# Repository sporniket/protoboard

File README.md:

# Sporniket's protoboard

> [WARNING] Please read carefully this note before using this project. It contains important facts.

Content

1. What is **Sporniket's protoboard**, and when to use it ?
2. What should you know before using **Sporniket's protoboard** ?
3. How to use **Sporniket's protoboard** ?
4. Known issues
5. Miscellanous

## 1. What is **Sporniket's protoboard**, and when to use it ?

**Sporniket's protoboard** is a custom prototyping board with 976 points arranged like a breadboard, that fits inside a 10cm×11cm rectangle.

This is a project designed with [Kicad](https://www.kicad.org/), version 7.

### Gallery

### Licence

**Sporniket's protoboard** is marked with CC0 1.0 Universal. To view a copy of this license, visit http://creativecommons.org/publicdomain/zero/1.0

**Sporniket's protoboard** is distributed in the hope that it will be useful, but WITHOUT ANY WARRANTY; without even the implied warranty of SAFETY, MERCHANTABILITY or FITNESS FOR A PARTICULAR PURPOSE.

### Releases notes

#### v1.0.0

* Initial release, schematics and gerbers.

## 2. What should you know before using **Sporniket's protoboard** ?

**Sporniket's protoboard** is designed using [Kicad](https://www.kicad.org/), version 7.

> Do not use **Sporniket's protoboard** if this project is not suitable for your project.

## 3. How to use **Sporniket's protoboard** ?

### From sources

To get the latest available models, one must clone the git repository.

	git clone https://github.com/sporniket/protoboard.git

Then, open the project in Kicad.

### From github releases

A github **schematic only** release (with `schematics` in the release tag and name) will provide a PDF of the schematics

A github **regular** release will provide :

* A standalone Kicad project
* A PDF of the schematics
* A PDF of the silkscreen
* If applicable, a Gerber for boardmanufacturer. Some details may have been adapted for a specific manufacturer.
* If applicable, a BOM, and pick an place files, likely for a specific manufacturer too.

## 4. Known issues
See the [project issues](https://github.com/sporniket/protoboard/issues) page.

## 5. Miscellanous

### Report issues
Use the [project issues](https://github.com/sporniket/protoboard/issues) page.

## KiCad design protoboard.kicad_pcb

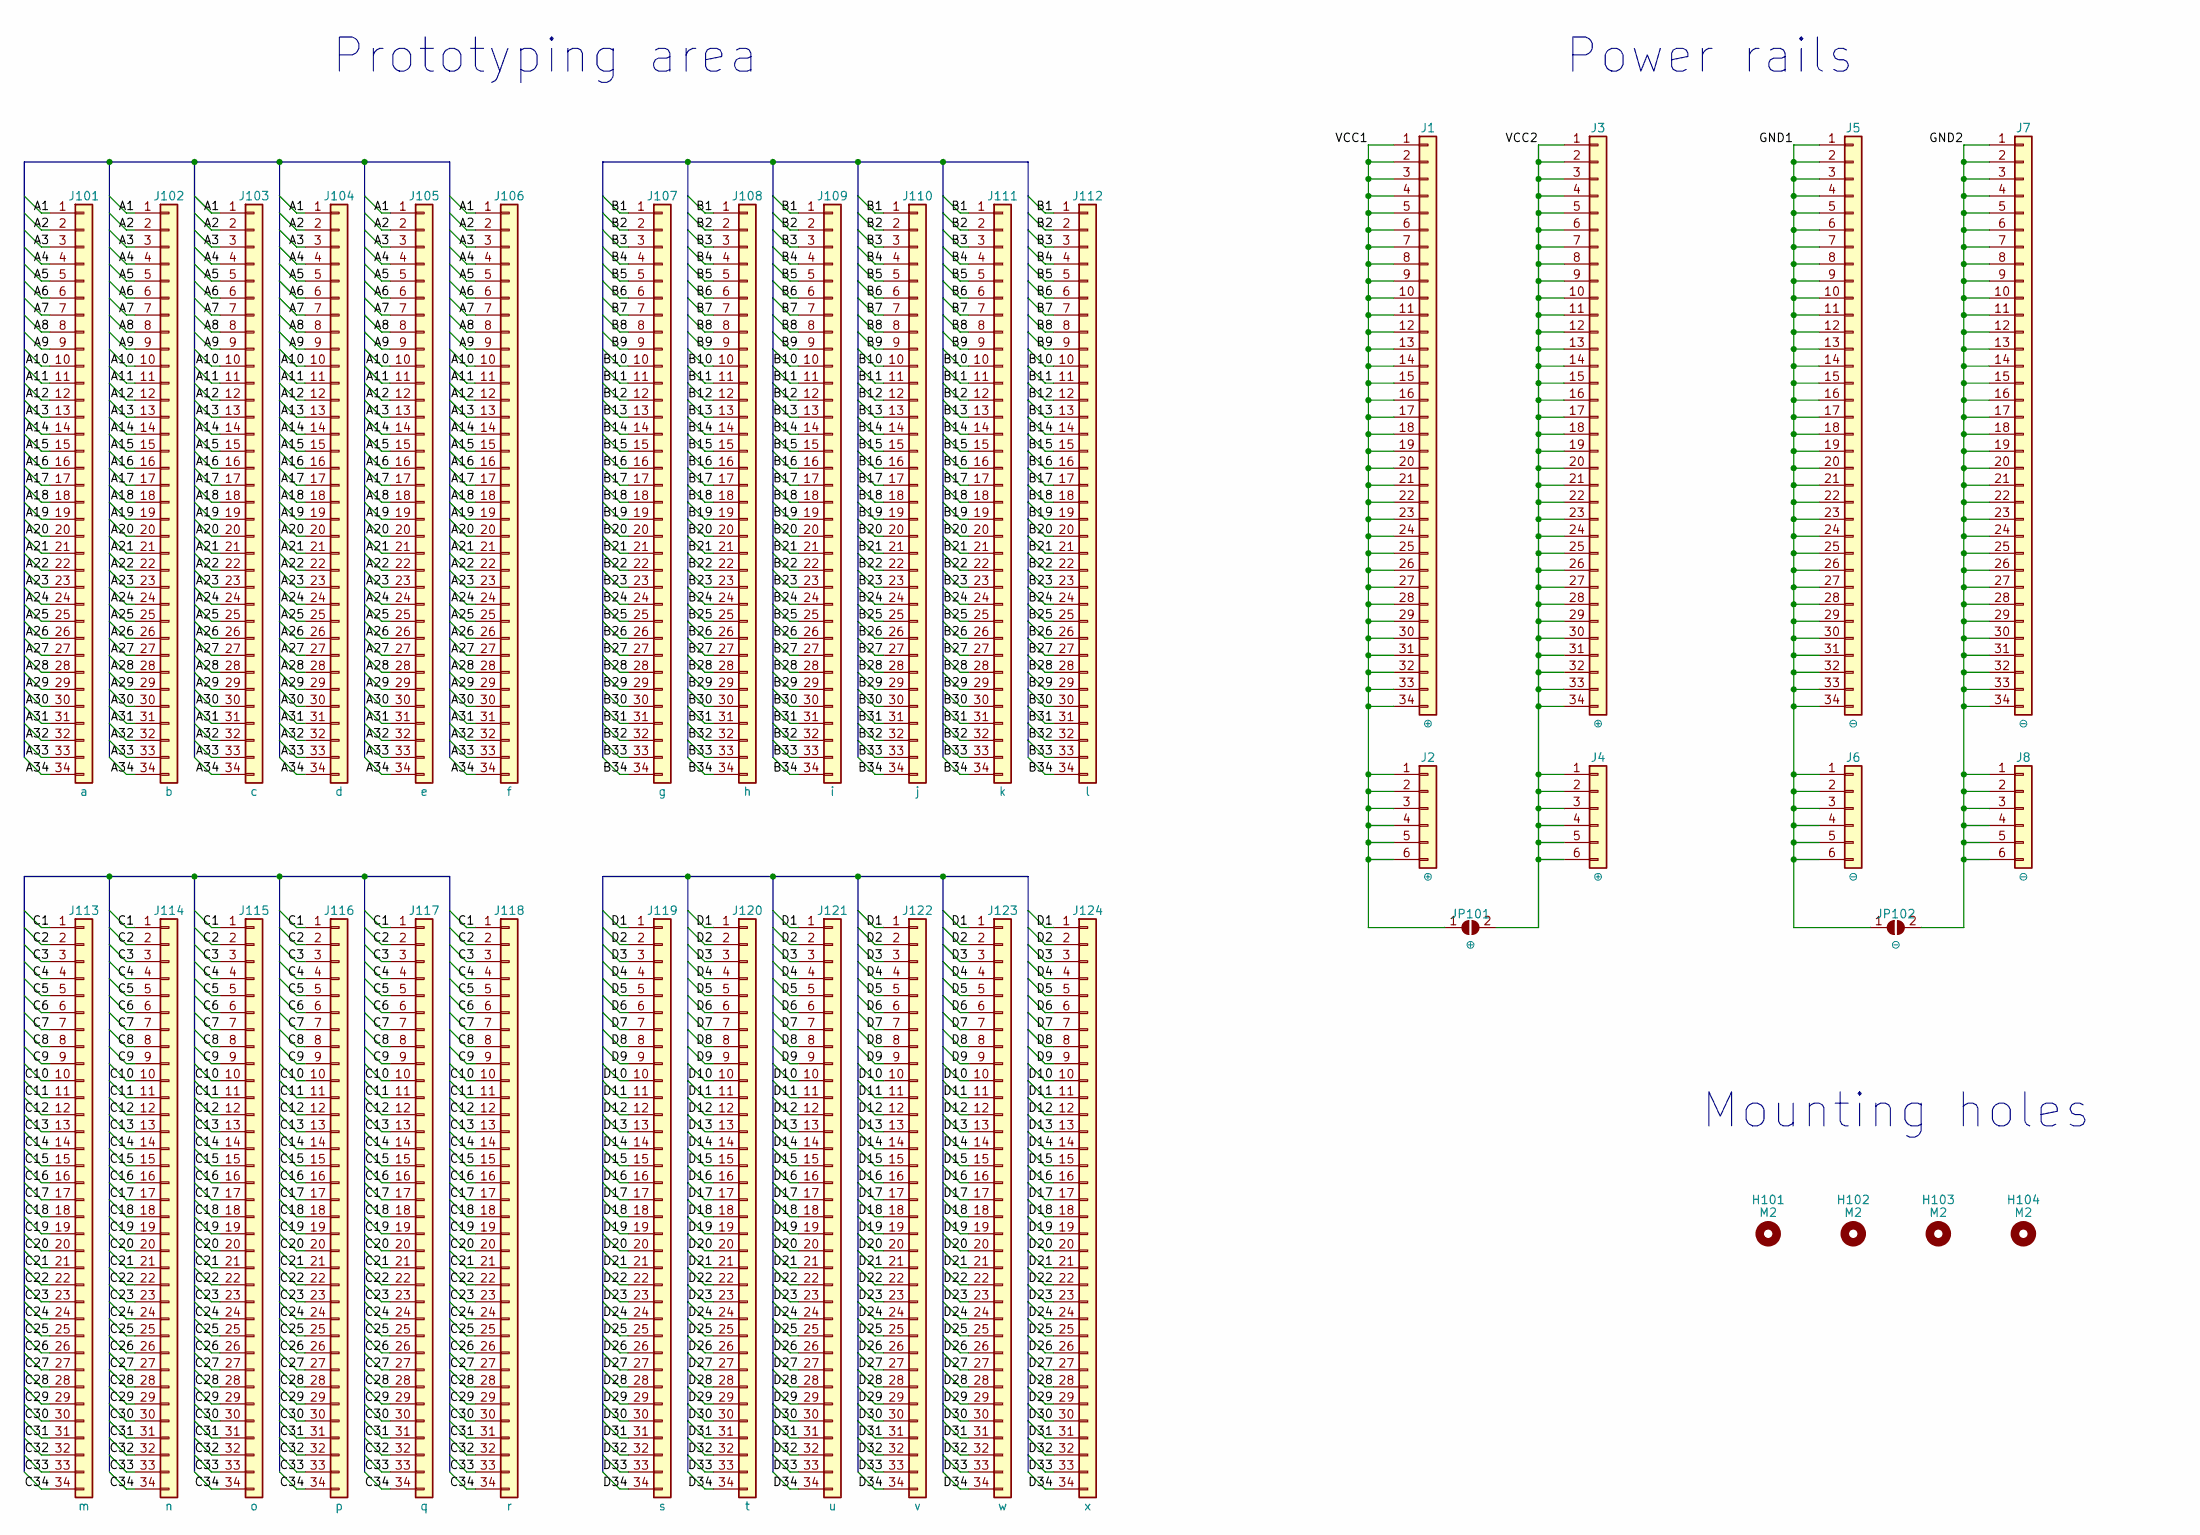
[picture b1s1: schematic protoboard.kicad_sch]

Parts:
H101, H102, H103, H104: M2; MountingHole_2.2mm_M2
J1, J3: ⊕; rows_of_pins_1x34
J2, J4: ⊕; rows_of_pins_1x6
J5, J7: ⊖; rows_of_pins_1x34
J6, J8: ⊖; rows_of_pins_1x6
J101: a; rows_of_pins_1x34
J102: b; rows_of_pins_1x34
J103: c; rows_of_pins_1x34
J104: d; rows_of_pins_1x34
J105: e; rows_of_pins_1x34
J106: f; rows_of_pins_1x34
J107: g; rows_of_pins_1x34
J108: h; rows_of_pins_1x34
J109: i; rows_of_pins_1x34
J110: j; rows_of_pins_1x34
J111: k; rows_of_pins_1x34
J112: l; rows_of_pins_1x34
J113: m; rows_of_pins_1x34
J114: n; rows_of_pins_1x34
J115: o; rows_of_pins_1x34
J116: p; rows_of_pins_1x34
J117: q; rows_of_pins_1x34
J118: r; rows_of_pins_1x34
J119: s; rows_of_pins_1x34
J120: t; rows_of_pins_1x34
J121: u; rows_of_pins_1x34
J122: v; rows_of_pins_1x34
J123: w; rows_of_pins_1x34
J124: x; rows_of_pins_1x34
JP101: ⊕; SolderJumper-2_P1.3mm_Open_RoundedPad1.0x1.5mm
JP102: ⊖; SolderJumper-2_P1.3mm_Open_RoundedPad1.0x1.5mm

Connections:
/A1: J101.1, J102.1, J103.1, J104.1, J105.1, J106.1
/A2: J101.2, J102.2, J103.2, J104.2, J105.2, J106.2
/A3: J101.3, J102.3, J103.3, J104.3, J105.3, J106.3
/A4: J101.4, J102.4, J103.4, J104.4, J105.4, J106.4
/A5: J101.5, J102.5, J103.5, J104.5, J105.5, J106.5
/A6: J101.6, J102.6, J103.6, J104.6, J105.6, J106.6
/A7: J101.7, J102.7, J103.7, J104.7, J105.7, J106.7
/A8: J101.8, J102.8, J103.8, J104.8, J105.8, J106.8
/A9: J101.9, J102.9, J103.9, J104.9, J105.9, J106.9
/A10: J101.10, J102.10, J103.10, J104.10, J105.10, J106.10
/A11: J101.11, J102.11, J103.11, J104.11, J105.11, J106.11
/A12: J101.12, J102.12, J103.12, J104.12, J105.12, J106.12
/A13: J101.13, J102.13, J103.13, J104.13, J105.13, J106.13
/A14: J101.14, J102.14, J103.14, J104.14, J105.14, J106.14
/A15: J101.15, J102.15, J103.15, J104.15, J105.15, J106.15
/A16: J101.16, J102.16, J103.16, J104.16, J105.16, J106.16
/A17: J101.17, J102.17, J103.17, J104.17, J105.17, J106.17
/A18: J101.18, J102.18, J103.18, J104.18, J105.18, J106.18
/A19: J101.19, J102.19, J103.19, J104.19, J105.19, J106.19
/A20: J101.20, J102.20, J103.20, J104.20, J105.20, J106.20
/A21: J101.21, J102.21, J103.21, J104.21, J105.21, J106.21
/A22: J101.22, J102.22, J103.22, J104.22, J105.22, J106.22
/A23: J101.23, J102.23, J103.23, J104.23, J105.23, J106.23
/A24: J101.24, J102.24, J103.24, J104.24, J105.24, J106.24
/A25: J101.25, J102.25, J103.25, J104.25, J105.25, J106.25
/A26: J101.26, J102.26, J103.26, J104.26, J105.26, J106.26
/A27: J101.27, J102.27, J103.27, J104.27, J105.27, J106.27
/A28: J101.28, J102.28, J103.28, J104.28, J105.28, J106.28
/A29: J101.29, J102.29, J103.29, J104.29, J105.29, J106.29
/A30: J101.30, J102.30, J103.30, J104.30, J105.30, J106.30
/A31: J101.31, J102.31, J103.31, J104.31, J105.31, J106.31
/A32: J101.32, J102.32, J103.32, J104.32, J105.32, J106.32
/A33: J101.33, J102.33, J103.33, J104.33, J105.33, J106.33
/A34: J101.34, J102.34, J103.34, J104.34, J105.34, J106.34
/B1: J107.1, J108.1, J109.1, J110.1, J111.1, J112.1
/B2: J107.2, J108.2, J109.2, J110.2, J111.2, J112.2
/B3: J107.3, J108.3, J109.3, J110.3, J111.3, J112.3
/B4: J107.4, J108.4, J109.4, J110.4, J111.4, J112.4
/B5: J107.5, J108.5, J109.5, J110.5, J111.5, J112.5
/B6: J107.6, J108.6, J109.6, J110.6, J111.6, J112.6
/B7: J107.7, J108.7, J109.7, J110.7, J111.7, J112.7
/B8: J107.8, J108.8, J109.8, J110.8, J111.8, J112.8
/B9: J107.9, J108.9, J109.9, J110.9, J111.9, J112.9
/B10: J107.10, J108.10, J109.10, J110.10, J111.10, J112.10
/B11: J107.11, J108.11, J109.11, J110.11, J111.11, J112.11
/B12: J107.12, J108.12, J109.12, J110.12, J111.12, J112.12
/B13: J107.13, J108.13, J109.13, J110.13, J111.13, J112.13
/B14: J107.14, J108.14, J109.14, J110.14, J111.14, J112.14
/B15: J107.15, J108.15, J109.15, J110.15, J111.15, J112.15
/B16: J107.16, J108.16, J109.16, J110.16, J111.16, J112.16
/B17: J107.17, J108.17, J109.17, J110.17, J111.17, J112.17
/B18: J107.18, J108.18, J109.18, J110.18, J111.18, J112.18
/B19: J107.19, J108.19, J109.19, J110.19, J111.19, J112.19
/B20: J107.20, J108.20, J109.20, J110.20, J111.20, J112.20
/B21: J107.21, J108.21, J109.21, J110.21, J111.21, J112.21
/B22: J107.22, J108.22, J109.22, J110.22, J111.22, J112.22
/B23: J107.23, J108.23, J109.23, J110.23, J111.23, J112.23
/B24: J107.24, J108.24, J109.24, J110.24, J111.24, J112.24
/B25: J107.25, J108.25, J109.25, J110.25, J111.25, J112.25
/B26: J107.26, J108.26, J109.26, J110.26, J111.26, J112.26
/B27: J107.27, J108.27, J109.27, J110.27, J111.27, J112.27
/B28: J107.28, J108.28, J109.28, J110.28, J111.28, J112.28
/B29: J107.29, J108.29, J109.29, J110.29, J111.29, J112.29
/B30: J107.30, J108.30, J109.30, J110.30, J111.30, J112.30
/B31: J107.31, J108.31, J109.31, J110.31, J111.31, J112.31
/B32: J107.32, J108.32, J109.32, J110.32, J111.32, J112.32
/B33: J107.33, J108.33, J109.33, J110.33, J111.33, J112.33
/B34: J107.34, J108.34, J109.34, J110.34, J111.34, J112.34
/C1: J113.1, J114.1, J115.1, J116.1, J117.1, J118.1
/C2: J113.2, J114.2, J115.2, J116.2, J117.2, J118.2
/C3: J113.3, J114.3, J115.3, J116.3, J117.3, J118.3
/C4: J113.4, J114.4, J115.4, J116.4, J117.4, J118.4
/C5: J113.5, J114.5, J115.5, J116.5, J117.5, J118.5
/C6: J113.6, J114.6, J115.6, J116.6, J117.6, J118.6
/C7: J113.7, J114.7, J115.7, J116.7, J117.7, J118.7
/C8: J113.8, J114.8, J115.8, J116.8, J117.8, J118.8
/C9: J113.9, J114.9, J115.9, J116.9, J117.9, J118.9
/C10: J113.10, J114.10, J115.10, J116.10, J117.10, J118.10
/C11: J113.11, J114.11, J115.11, J116.11, J117.11, J118.11
/C12: J113.12, J114.12, J115.12, J116.12, J117.12, J118.12
/C13: J113.13, J114.13, J115.13, J116.13, J117.13, J118.13
/C14: J113.14, J114.14, J115.14, J116.14, J117.14, J118.14
/C15: J113.15, J114.15, J115.15, J116.15, J117.15, J118.15
/C16: J113.16, J114.16, J115.16, J116.16, J117.16, J118.16
/C17: J113.17, J114.17, J115.17, J116.17, J117.17, J118.17
/C18: J113.18, J114.18, J115.18, J116.18, J117.18, J118.18
/C19: J113.19, J114.19, J115.19, J116.19, J117.19, J118.19
/C20: J113.20, J114.20, J115.20, J116.20, J117.20, J118.20
/C21: J113.21, J114.21, J115.21, J116.21, J117.21, J118.21
/C22: J113.22, J114.22, J115.22, J116.22, J117.22, J118.22
/C23: J113.23, J114.23, J115.23, J116.23, J117.23, J118.23
/C24: J113.24, J114.24, J115.24, J116.24, J117.24, J118.24
/C25: J113.25, J114.25, J115.25, J116.25, J117.25, J118.25
/C26: J113.26, J114.26, J115.26, J116.26, J117.26, J118.26
/C27: J113.27, J114.27, J115.27, J116.27, J117.27, J118.27
/C28: J113.28, J114.28, J115.28, J116.28, J117.28, J118.28
/C29: J113.29, J114.29, J115.29, J116.29, J117.29, J118.29
/C30: J113.30, J114.30, J115.30, J116.30, J117.30, J118.30
/C31: J113.31, J114.31, J115.31, J116.31, J117.31, J118.31
/C32: J113.32, J114.32, J115.32, J116.32, J117.32, J118.32
/C33: J113.33, J114.33, J115.33, J116.33, J117.33, J118.33
/C34: J113.34, J114.34, J115.34, J116.34, J117.34, J118.34
/D1: J119.1, J120.1, J121.1, J122.1, J123.1, J124.1
/D2: J119.2, J120.2, J121.2, J122.2, J123.2, J124.2
/D3: J119.3, J120.3, J121.3, J122.3, J123.3, J124.3
/D4: J119.4, J120.4, J121.4, J122.4, J123.4, J124.4
/D5: J119.5, J120.5, J121.5, J122.5, J123.5, J124.5
/D6: J119.6, J120.6, J121.6, J122.6, J123.6, J124.6
/D7: J119.7, J120.7, J121.7, J122.7, J123.7, J124.7
/D8: J119.8, J120.8, J121.8, J122.8, J123.8, J124.8
/D9: J119.9, J120.9, J121.9, J122.9, J123.9, J124.9
/D10: J119.10, J120.10, J121.10, J122.10, J123.10, J124.10
/D11: J119.11, J120.11, J121.11, J122.11, J123.11, J124.11
/D12: J119.12, J120.12, J121.12, J122.12, J123.12, J124.12
/D13: J119.13, J120.13, J121.13, J122.13, J123.13, J124.13
/D14: J119.14, J120.14, J121.14, J122.14, J123.14, J124.14
/D15: J119.15, J120.15, J121.15, J122.15, J123.15, J124.15
/D16: J119.16, J120.16, J121.16, J122.16, J123.16, J124.16
/D17: J119.17, J120.17, J121.17, J122.17, J123.17, J124.17
/D18: J119.18, J120.18, J121.18, J122.18, J123.18, J124.18
/D19: J119.19, J120.19, J121.19, J122.19, J123.19, J124.19
/D20: J119.20, J120.20, J121.20, J122.20, J123.20, J124.20
/D21: J119.21, J120.21, J121.21, J122.21, J123.21, J124.21
/D22: J119.22, J120.22, J121.22, J122.22, J123.22, J124.22
/D23: J119.23, J120.23, J121.23, J122.23, J123.23, J124.23
/D24: J119.24, J120.24, J121.24, J122.24, J123.24, J124.24
/D25: J119.25, J120.25, J121.25, J122.25, J123.25, J124.25
/D26: J119.26, J120.26, J121.26, J122.26, J123.26, J124.26
/D27: J119.27, J120.27, J121.27, J122.27, J123.27, J124.27
/D28: J119.28, J120.28, J121.28, J122.28, J123.28, J124.28
/D29: J119.29, J120.29, J121.29, J122.29, J123.29, J124.29
/D30: J119.30, J120.30, J121.30, J122.30, J123.30, J124.30
/D31: J119.31, J120.31, J121.31, J122.31, J123.31, J124.31
/D32: J119.32, J120.32, J121.32, J122.32, J123.32, J124.32
/D33: J119.33, J120.33, J121.33, J122.33, J123.33, J124.33
/D34: J119.34, J120.34, J121.34, J122.34, J123.34, J124.34
unnamed: J1.1, J1.2, J1.3, J1.4, J1.5, J1.6, J1.7, J1.8, J1.9, J1.10, J1.11, J1.12, J1.13, J1.14, J1.15, J1.16, J1.17, J1.18, J1.19, J1.20, J1.21, J1.22, J1.23, J1.24, J1.25, J1.26, J1.27, J1.28, J1.29, J1.30, J1.31, J1.32, J1.33, J1.34, J2.1, J2.2, J2.3, J2.4, J2.5, J2.6, JP101.1 (A)
unnamed: J3.1, J3.2, J3.3, J3.4, J3.5, J3.6, J3.7, J3.8, J3.9, J3.10, J3.11, J3.12, J3.13, J3.14, J3.15, J3.16, J3.17, J3.18, J3.19, J3.20, J3.21, J3.22, J3.23, J3.24, J3.25, J3.26, J3.27, J3.28, J3.29, J3.30, J3.31, J3.32, J3.33, J3.34, J4.1, J4.2, J4.3, J4.4, J4.5, J4.6, JP101.2 (B)
unnamed: J5.1, J5.2, J5.3, J5.4, J5.5, J5.6, J5.7, J5.8, J5.9, J5.10, J5.11, J5.12, J5.13, J5.14, J5.15, J5.16, J5.17, J5.18, J5.19, J5.20, J5.21, J5.22, J5.23, J5.24, J5.25, J5.26, J5.27, J5.28, J5.29, J5.30, J5.31, J5.32, J5.33, J5.34, J6.1, J6.2, J6.3, J6.4, J6.5, J6.6, JP102.1 (A)
unnamed: J7.1, J7.2, J7.3, J7.4, J7.5, J7.6, J7.7, J7.8, J7.9, J7.10, J7.11, J7.12, J7.13, J7.14, J7.15, J7.16, J7.17, J7.18, J7.19, J7.20, J7.21, J7.22, J7.23, J7.24, J7.25, J7.26, J7.27, J7.28, J7.29, J7.30, J7.31, J7.32, J7.33, J7.34, J8.1, J8.2, J8.3, J8.4, J8.5, J8.6, JP102.2 (B)

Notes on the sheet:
Power rails
Mounting holes
Prototyping area

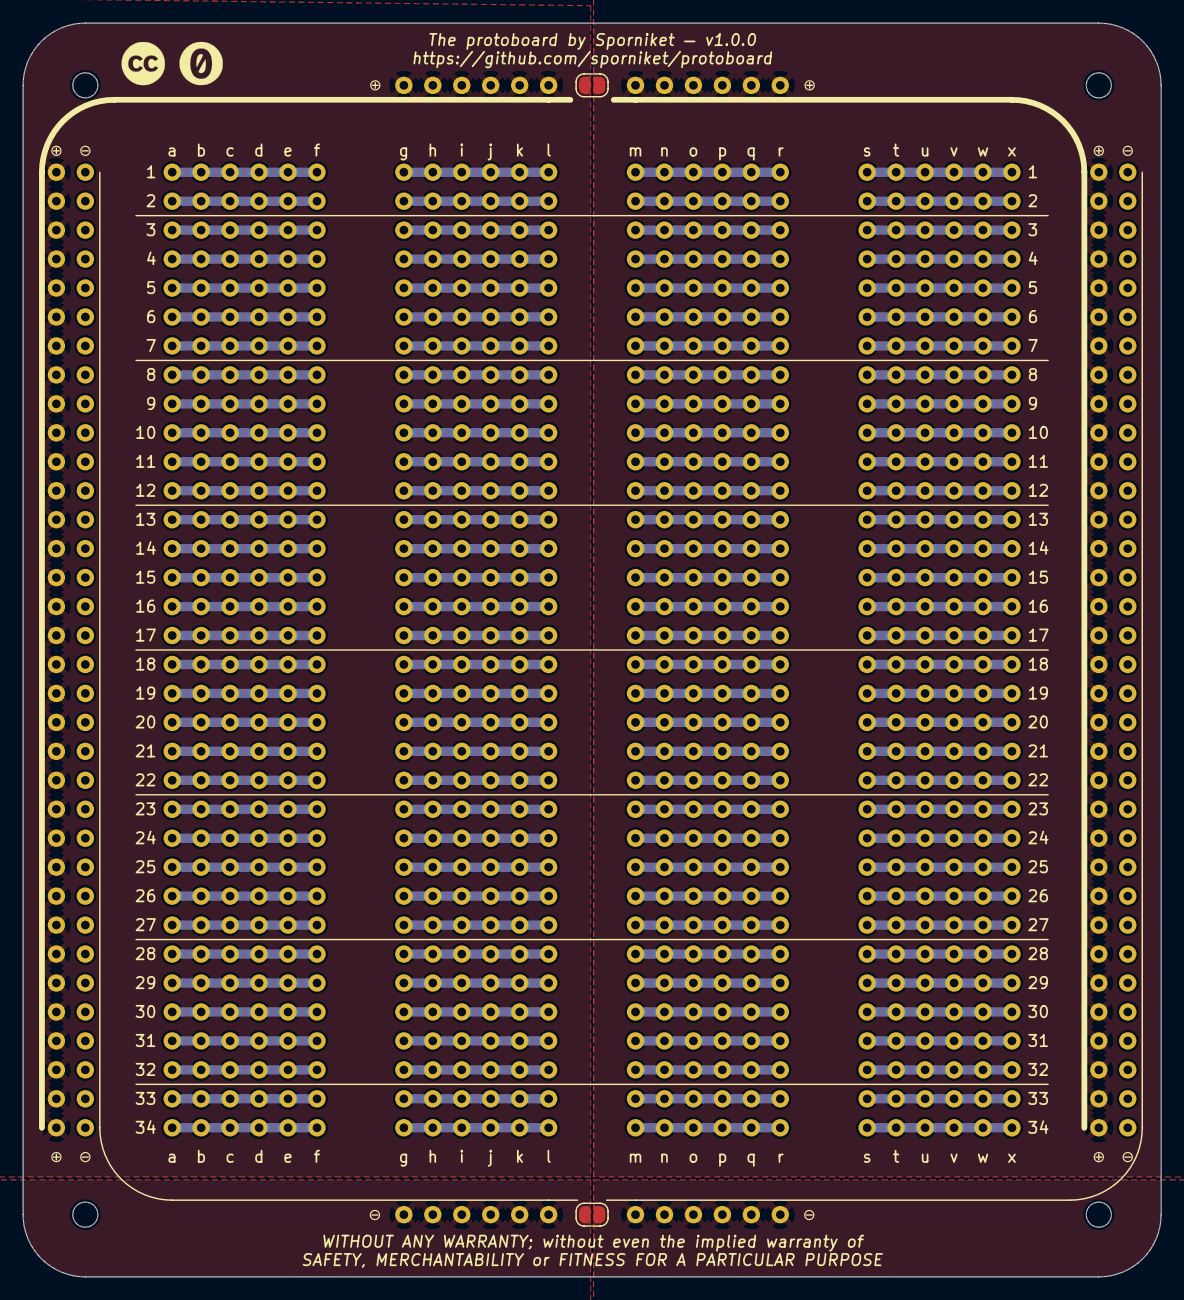
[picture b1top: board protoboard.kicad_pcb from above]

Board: 2 copper layers, 99.8 x 110.0 mm, 38 parts (0 on the bottom side), 140 nets.

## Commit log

2022-09-15 schematics + pcb placement and texts
2022-09-16 wiring all the bussed connectors
2022-09-16 remove unnecessary submodules
2022-09-16 Standard README
2022-09-16 Adjust label contents and position, document annotation with actual repository
2022-09-16 copper pours for each power rail
2022-10-07 ready to release
2022-10-07 prepare release : README
2022-10-07 pcb size is 10x11cm
2023-12-28 illustrate the README
2023-12-28 migrate to Kicad 7
2023-12-29 wip -- reworking prototyping area
2023-12-29 done extending prototype area
